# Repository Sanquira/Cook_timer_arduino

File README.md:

# Cook_timer_arduino

Project of Cooking timer based on Arduino Nano ATmega328.

Project is designed with focus on modularity. Therefore there are few independent modules:

Event       - Simple event template. Used for firing events like button pressed, buzzer melody ended (or was ended),
              timer timed out.

Button      - Module which allows you to register button on pin with debounce feature and event response in program.

Buzzer      - Module for sound output with support of melody and/or cycle play.

TimerLogic  - Module for time measure designed on minutes scale. Fire event when timer ends.
              Inner timer count in millis. There is support for "live" add/remove time.
              It will return you remaining time in minutes and in seconds and second ticking indicator.
              Timer reset itself when stopped.

LedDisp     - Module for 4 digits 7-segments LED display. It uses multiplex technology so it needs 8 + 4 pins when registering.

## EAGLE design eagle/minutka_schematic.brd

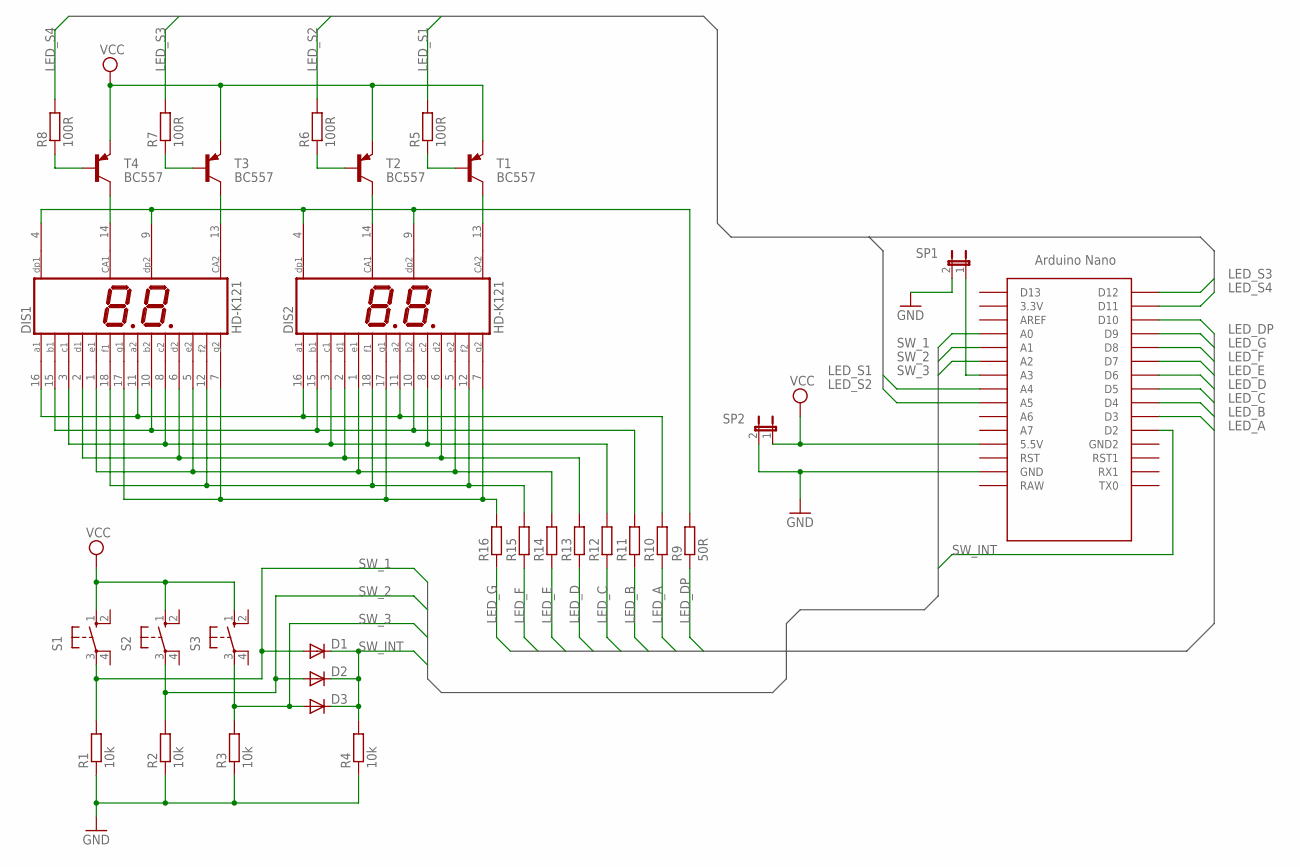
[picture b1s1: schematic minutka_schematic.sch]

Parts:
D1, D2, D3: DIODE-D-5; D-5
DIS1, DIS2: HD-K121; HDSP-R
R1, R2, R3, R4: 10k; 0204/7
R5, R6, R7, R8: 100R; 0204/7
R9: 50R; 0204/7
R10, R11, R12, R13, R14, R15, R16: R-EU_0204/7; 0204/7
S1, S2, S3: 10-XX; B3F-10XX
SP1, SP2: JP1E; JP1
T1, T2, T3, T4: BC557; TO92-EBC
U$1: NANO

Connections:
GND: R1.1, R2.1, R3.1, R4.1, SP1.2, SP2.2, U$1.GND
LED_A: R10.1, U$1.D3
LED_B: R11.1, U$1.D4
LED_C: R12.1, U$1.D5
LED_D: R13.1, U$1.D6
LED_DP: R9.1, U$1.D10
LED_E: R14.1, U$1.D7
LED_F: R15.1, U$1.D8
LED_G: R16.1, U$1.D9
LED_S1: R5.2, U$1.A4
LED_S2: R6.2, U$1.A5
LED_S3: R7.2, U$1.D12
LED_S4: R8.2, U$1.D11
unnamed: DIS1.11 (A2), DIS1.16 (A1), DIS2.11 (A2), DIS2.16 (A1), R10.2
unnamed: DIS1.10 (B2), DIS1.15 (B1), DIS2.10 (B2), DIS2.15 (B1), R11.2
unnamed: DIS1.3 (C1), DIS1.8 (C2), DIS2.3 (C1), DIS2.8 (C2), R12.2
unnamed: DIS1.2 (D1), DIS1.6 (D2), DIS2.2 (D1), DIS2.6 (D2), R13.2
unnamed: DIS1.1 (E1), DIS1.5 (E2), DIS2.1 (E1), DIS2.5 (E2), R14.2
unnamed: DIS1.12 (F2), DIS1.18 (F1), DIS2.12 (F2), DIS2.18 (F1), R15.2
unnamed: DIS1.7 (G2), DIS1.17 (G1), DIS2.7 (G2), DIS2.17 (G1), R16.2
unnamed: DIS1.4 (DP1), DIS1.9 (DP2), DIS2.4 (DP1), DIS2.9 (DP2), R9.2
unnamed: DIS2.13 (CA2), T1.C
unnamed: DIS2.14 (CA1), T2.C
unnamed: DIS1.13 (CA2), T3.C
unnamed: DIS1.14 (CA1), T4.C
unnamed: R7.1, T3.B
unnamed: R8.1, T4.B
unnamed: R6.1, T2.B
unnamed: R5.1, T1.B
unnamed: SP1.1, U$1.A3
SW_1: D1.A, R1.2, S1.3, U$1.A0
SW_2: D2.A, R2.2, S2.3, U$1.A1
SW_3: D3.A, R3.2, S3.3, U$1.A2
SW_INT: D1.C, D2.C, D3.C, R4.2, U$1.D2
VCC: S1.1 (S), S2.1 (S), S3.1 (S), SP2.1, T1.E, T2.E, T3.E, T4.E, U$1.5V (5.5V)

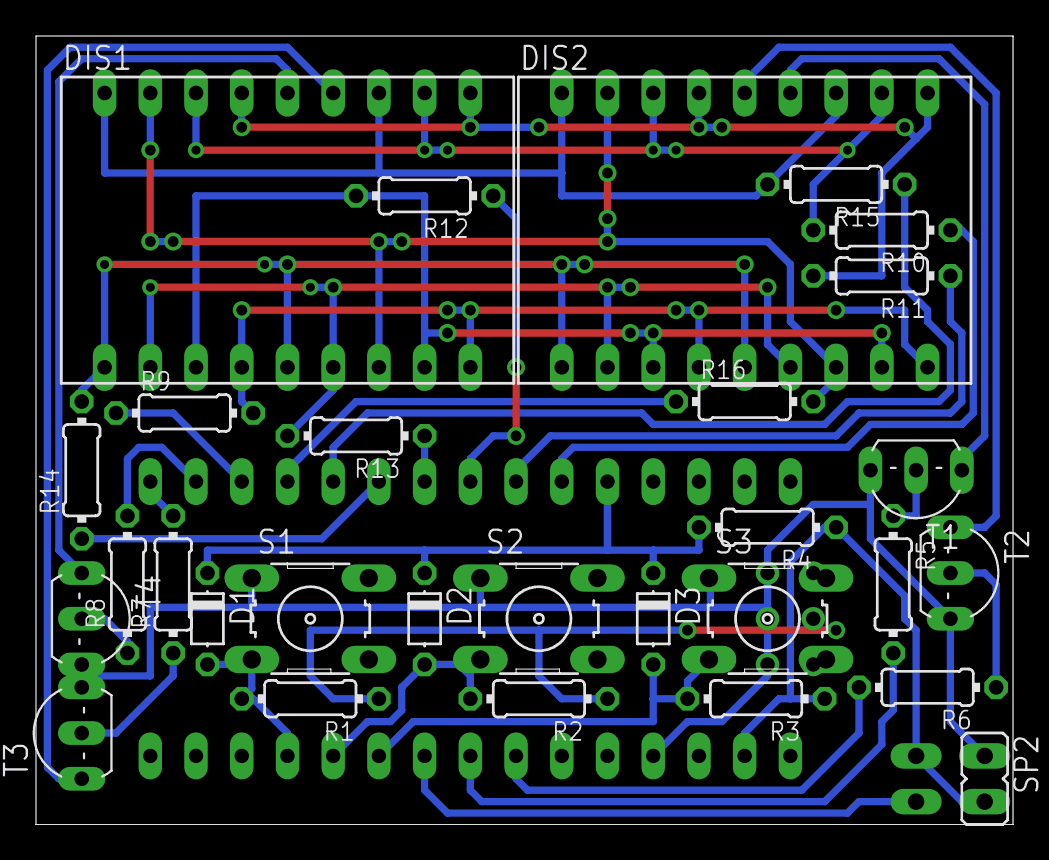
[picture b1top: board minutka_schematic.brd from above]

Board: 2 copper layers, 54.3 x 43.8 mm, 31 parts (1 on the bottom side), 35 nets.

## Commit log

2017-12-06 Finished project of "cooking timer".
2017-12-06 Removed some comments forgottend from development.
2017-12-14 Added eagle schematic and board.
    Renamed project code folder
